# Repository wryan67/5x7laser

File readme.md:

## 5x7 laser gun

This lasergun can be produced using 5" x 7" sheets of plastic or basswood.

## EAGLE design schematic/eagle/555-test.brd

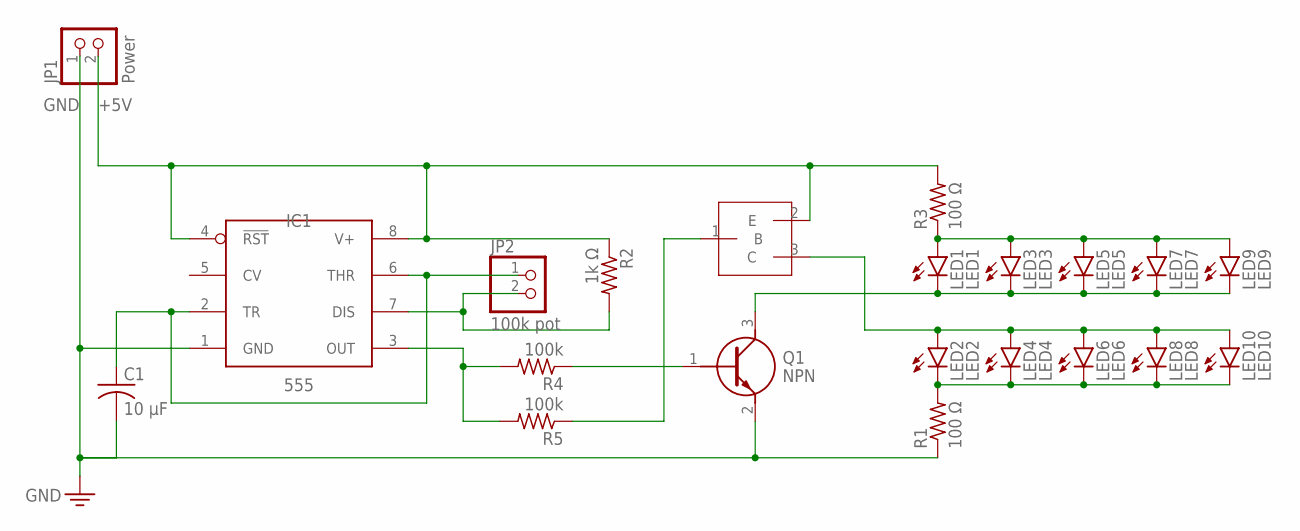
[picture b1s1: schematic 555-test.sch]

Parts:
C1: 10 μF; CAPC2012X110
IC1: 555; SOIC127P599X175-8N
JP1: Power; 1X02
JP2: 100k pot; 1X02
LED1: LED1; CHIP-LED0805
LED2: LED2; CHIP-LED0805
LED3: LED3; CHIP-LED0805
LED4: LED4; CHIP-LED0805
LED5: LED5; CHIP-LED0805
LED6: LED6; CHIP-LED0805
LED7: LED7; CHIP-LED0805
LED8: LED8; CHIP-LED0805
LED9: LED9; CHIP-LED0805
LED10: LED10; CHIP-LED0805
Q1: NPN; PMBT2222A215
R1, R3: 100 Ω; M0805
R2: 1k Ω; M0805
R4, R5: 100k; M0805
U$1: PNP; SOT95P230X110-3N

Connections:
+5V: IC1.4 (!RST), IC1.8 (V+), JP1.2, R2.1, R3.2, U$1.2 (E)
GND: C1.2, IC1.1 (GND), JP1.1, Q1.2 (E), R1.1
unnamed: C1.1, IC1.2 (TR), IC1.6 (THR), JP2.1
unnamed: IC1.3 (OUT), R4.2, R5.2
unnamed: Q1.1 (B), R4.1
unnamed: LED2.C, LED4.C, LED6.C, LED8.C, LED10.C, R1.2
unnamed: IC1.7 (DIS), JP2.2, R2.2
unnamed: LED1.A, LED3.A, LED5.A, LED7.A, LED9.A, R3.1
unnamed: LED1.C, LED3.C, LED5.C, LED7.C, LED9.C, Q1.3 (C)
unnamed: R5.1, U$1.1 (B)
unnamed: LED2.A, LED4.A, LED6.A, LED8.A, LED10.A, U$1.3 (C)

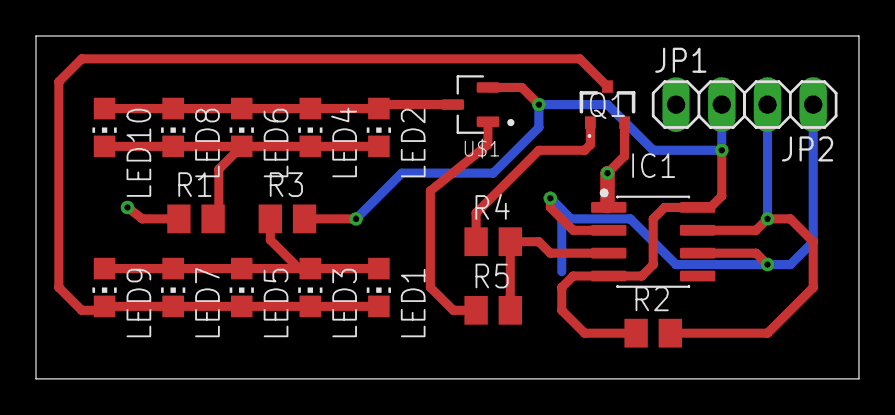
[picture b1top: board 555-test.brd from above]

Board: 2 copper layers, 45.7 x 19.1 mm, 21 parts (1 on the bottom side), 11 nets.

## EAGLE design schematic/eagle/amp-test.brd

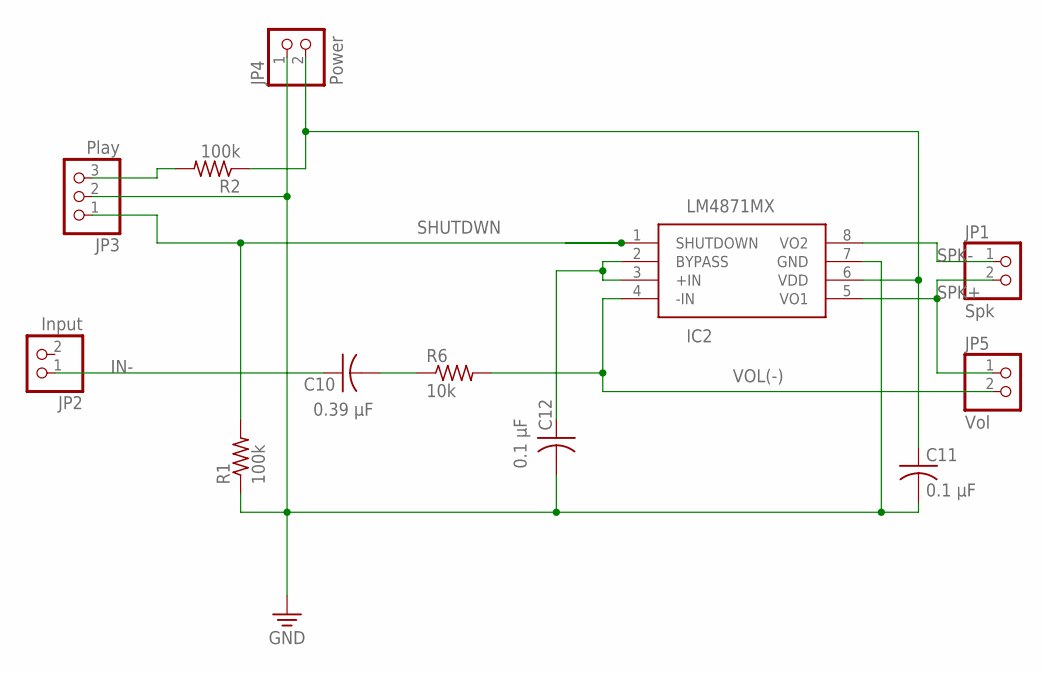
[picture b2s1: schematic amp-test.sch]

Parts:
C10: 0.39 μF; C0805
C11, C12: 0.1 μF; C0805
IC2: LM4871MX; SOIC127P600X175-8N
JP1: Spk; 1X02
JP2: Input; 1X02
JP3: Play; 1X03
JP4: Power; 1X02
JP5: Vol; 1X02
R1, R2: 100k; R0805
R6: 10k; R0805

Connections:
+5V: C11.1, IC2.6 (VDD), JP4.2, R2.1
GND: C11.2, C12.2, IC2.7 (GND), JP3.2, JP4.1, R1.1
IN-: C10.1, JP2.1
unnamed: JP3.3, R2.2
unnamed: C10.2, R6.1
unnamed: C12.1, IC2.2 (BYPASS), IC2.3 (+IN)
SHUTDWN: IC2.1 (SHUTDOWN), JP3.1, R1.2
SPK+: IC2.5 (VO1), JP1.2, JP5.1
SPK-: IC2.8 (VO2), JP1.1
VOL(-): IC2.4 (-IN), JP5.2, R6.2

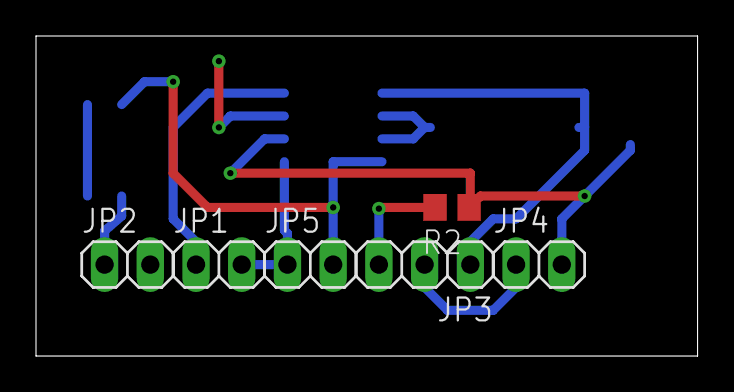
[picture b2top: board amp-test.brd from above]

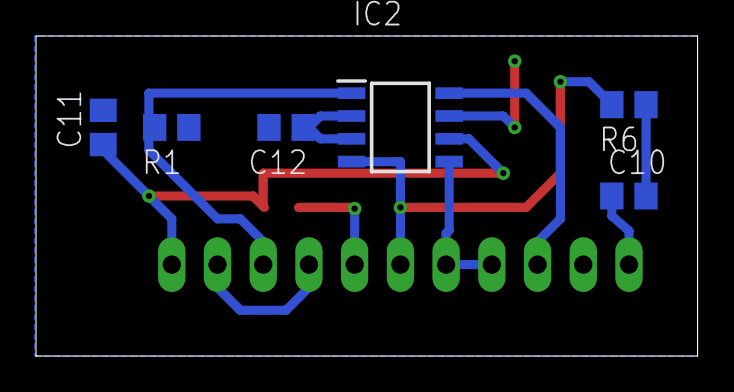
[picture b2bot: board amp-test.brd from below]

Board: 2 copper layers, 36.8 x 17.8 mm, 12 parts (6 on the bottom side), 10 nets.

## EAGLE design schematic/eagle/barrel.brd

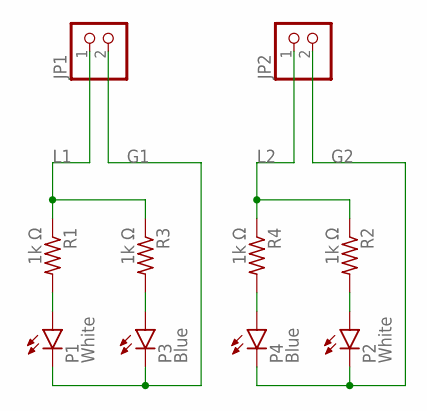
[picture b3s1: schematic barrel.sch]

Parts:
JP1, JP2: PINHD-1X2; 1X02
P1, P2: White; CHIP-LED0805
P3, P4: Blue; CHIP-LED0805
R1, R2, R3, R4: 1k Ω; M0805

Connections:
G1: JP1.2, P1.C, P3.C
G2: JP2.2, P2.C, P4.C
L1: JP1.1, R1.1, R3.1
L2: JP2.1, R2.1, R4.1
unnamed: P1.A, R1.2
unnamed: P3.A, R3.2
unnamed: P2.A, R2.2
unnamed: P4.A, R4.2

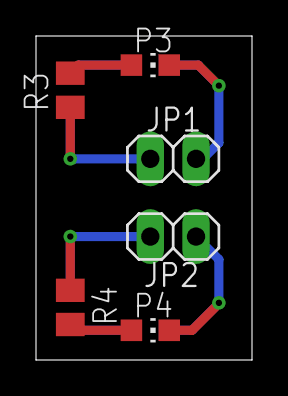
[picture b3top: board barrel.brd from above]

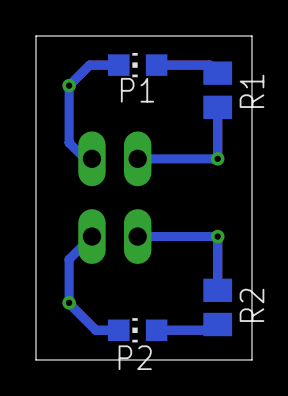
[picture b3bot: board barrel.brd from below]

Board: 2 copper layers, 12.0 x 18.0 mm, 10 parts (4 on the bottom side), 8 nets.

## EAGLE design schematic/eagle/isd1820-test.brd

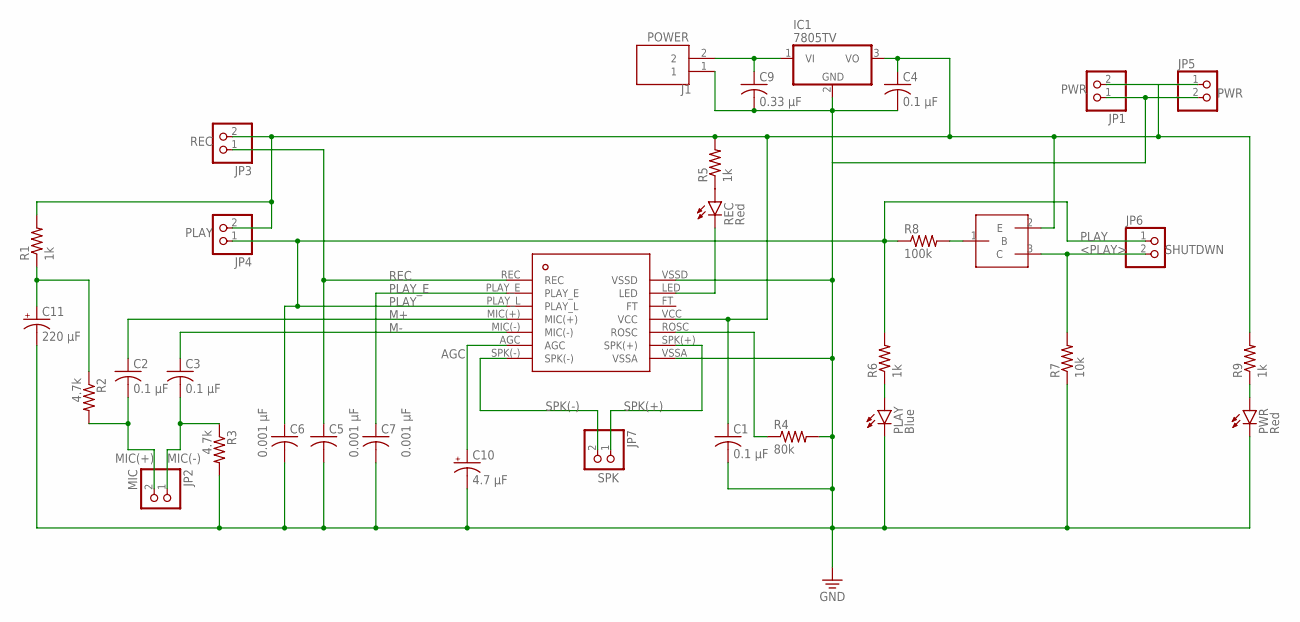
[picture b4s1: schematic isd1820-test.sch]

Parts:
C1, C2, C3, C4: 0.1 μF; C0805
C5, C6, C7: 0.001 μF; C0805
C9: 0.33 μF; C0805
C10: 4.7 μF; E2,5-5
C11: 220 μF; E2,5-5
IC1: 7805TV; TO220V
J1: POWER; CUI_TB004-508-02BE
JP1, JP5: PWR; 1X02
JP2: MIC; 1X02
JP3: REC; 1X02
JP4: PLAY; 1X02
JP6: SHUTDWN; 1X02
JP7: SPK; 1X02
PLAY: Blue; CHIP-LED0805
PWR: Red; CHIP-LED0805
R1, R5, R6, R9: 1k; R0805
R2, R3: 4.7k; R0805
R4: 80k; R0805
R7: 10k; R0805
R8: 100k; R0805
REC: Red; CHIP-LED0805
U$1: ISD1820PY
U$2: PNP; SOT95P230X110-3N

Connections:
+5V: C1.1, C4.1, IC1.3 (VO), JP1.2, JP3.2, JP4.2, JP5.1, R1.2, R5.2, R9.2, U$1.VCC, U$2.2 (E)
<PLAY>: JP6.2, R7.2, U$2.3 (C)
AGC: C10.+, U$1.AGC
GND: C1.2, C4.2, C5.2, C6.2, C7.2, C9.2, C10.-, C11.-, IC1.2 (GND), J1.1, JP1.1, JP5.2, PLAY.C, PWR.C, R3.2, R4.2, R7.1, U$1.VSSA, U$1.VSSD
M+: C2.1, U$1.MIC(+)
M-: C3.1, U$1.MIC(-)
MIC(+): C2.2, JP2.2, R2.2
MIC(-): C3.2, JP2.1, R3.1
unnamed: PLAY.A, R6.1
unnamed: PWR.A, R9.1
unnamed: R8.2, U$2.1 (B)
unnamed: R4.1, U$1.ROSC
unnamed: C9.1, IC1.1 (VI), J1.2
unnamed: C11.+, R1.1, R2.1
unnamed: R5.1, REC.A
unnamed: REC.C, U$1.LED
PLAY: C6.1, JP4.1, JP6.1, R6.2, R8.1, U$1.PLAY_L
PLAY_E: C7.1, U$1.PLAY_E
REC: C5.1, JP3.1, U$1.REC
SPK(+): JP7.1, U$1.SPK(+)
SPK(-): JP7.2, U$1.SPK(-)

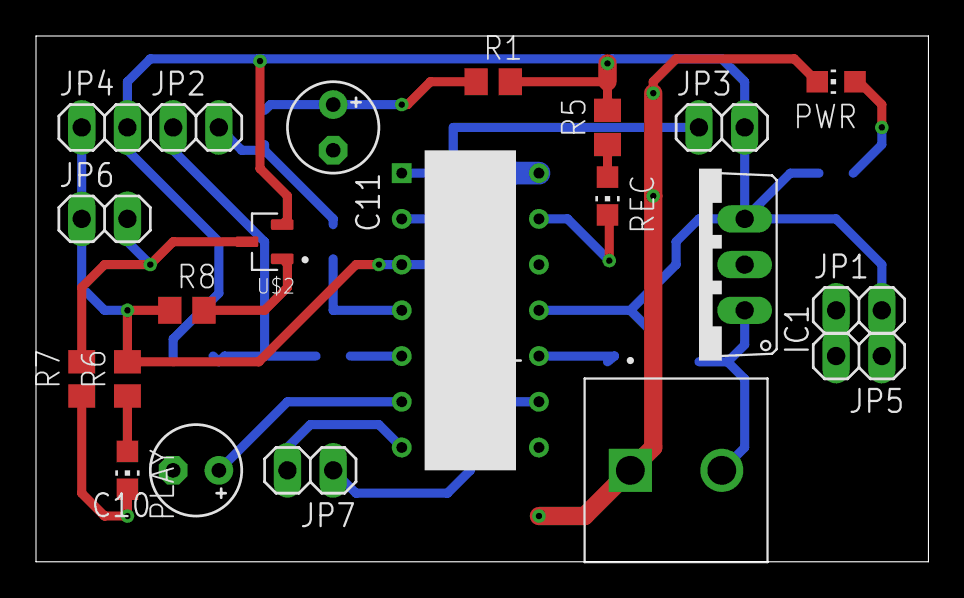
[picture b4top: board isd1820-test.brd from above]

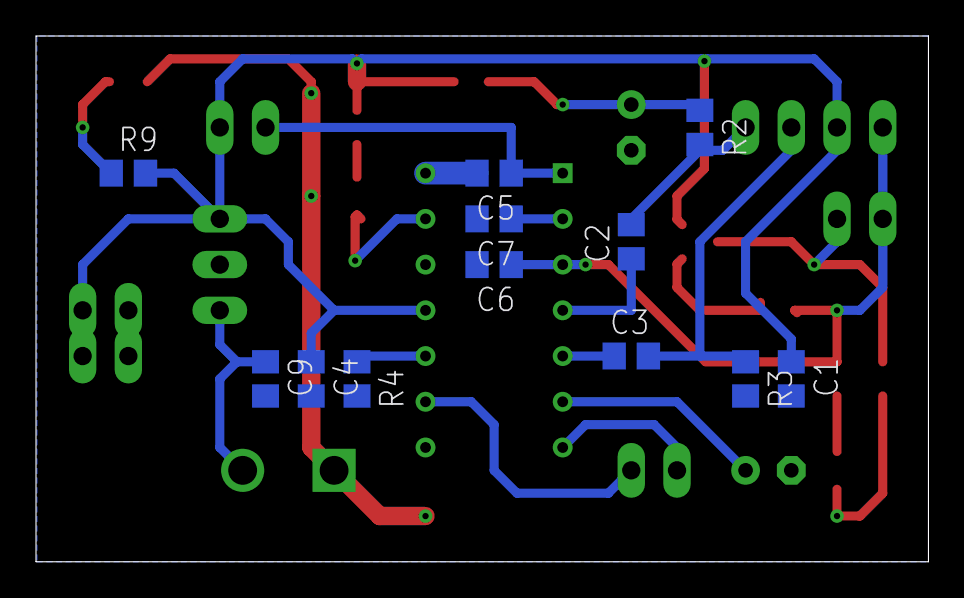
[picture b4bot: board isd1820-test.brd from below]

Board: 2 copper layers, 49.6 x 29.2 mm, 33 parts (12 on the bottom side), 21 nets.

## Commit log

2023-05-02 5x7laser

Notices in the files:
parts and their libraries:
SparkFun-PowerSymbols: Licensing: Creative Commons ShareAlike 4.0 International - https://creativecommons.org/licenses/by-sa/4.0
